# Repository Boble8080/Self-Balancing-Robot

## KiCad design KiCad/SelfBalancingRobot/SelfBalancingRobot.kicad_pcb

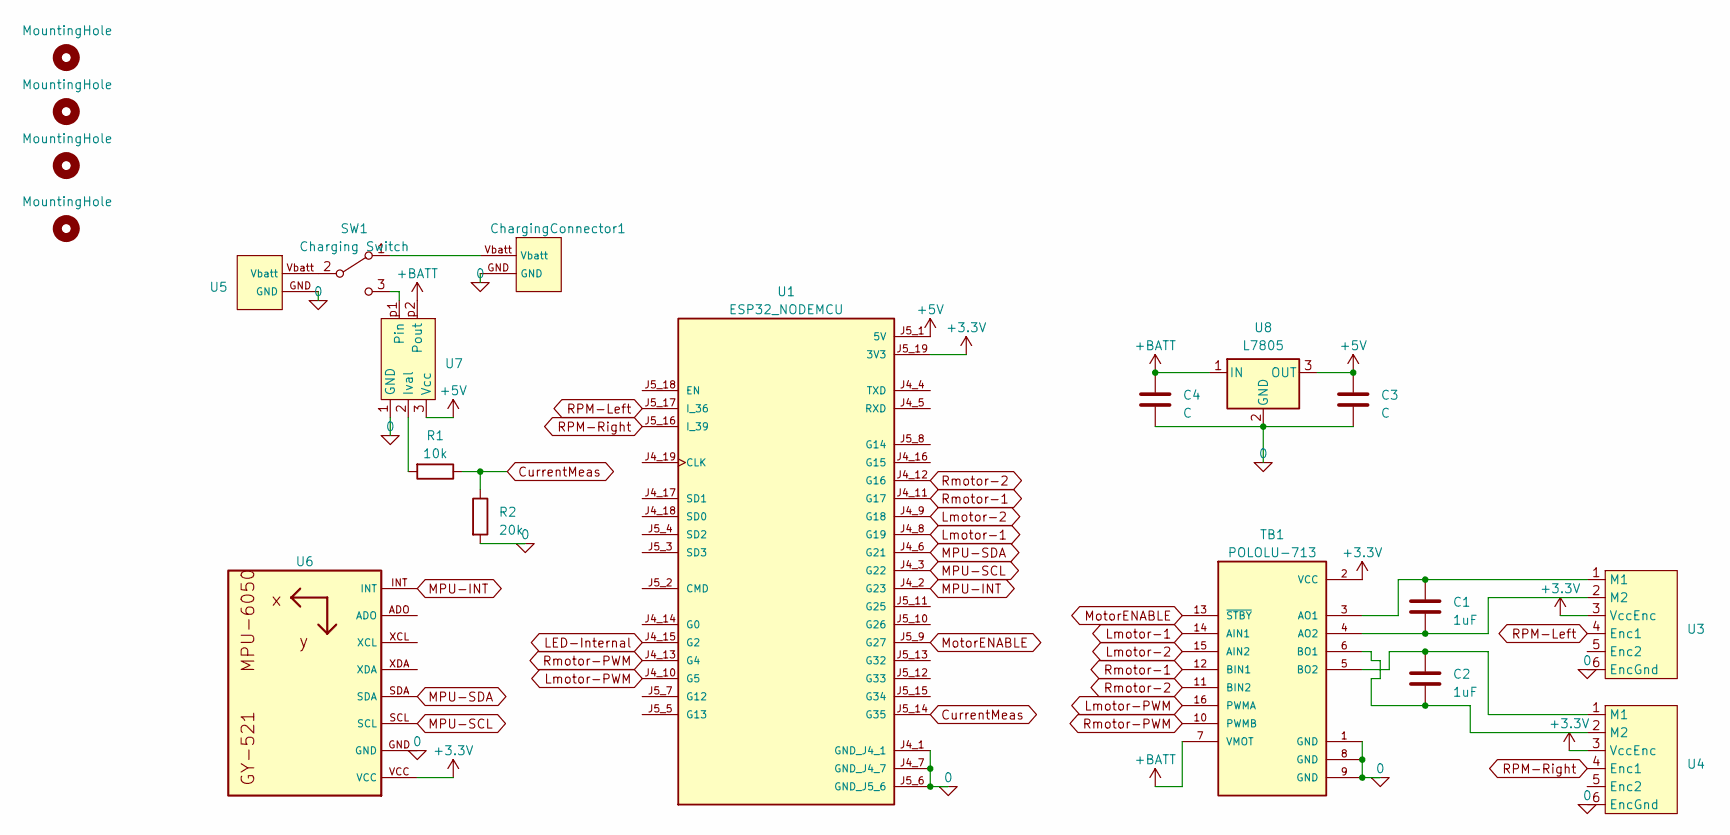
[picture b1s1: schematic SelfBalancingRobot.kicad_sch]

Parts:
C1, C2: 1uF; C_Disc_D6.0mm_W4.4mm_P5.00mm
C3, C4: C; CP_Radial_D6.3mm_P2.50mm
ChargingConnector1: ChargingConnector
H1, H2, H3, H4: MountingHole; MountingHole_3.2mm_M3_DIN965_Pad_TopBottom
R1: 10k; R_Axial_DIN0207_L6.3mm_D2.5mm_P7.62mm_Horizontal
R2: 20k; R_Axial_DIN0207_L6.3mm_D2.5mm_P7.62mm_Horizontal
SW1: Charging Switch; PhoenixContact_MSTBA_2,5_3-G-5,08_1x03_P5.08mm_Horizontal
TB1: POLOLU-713; SHIELD_POLOLU-713
U1: ESP32_NODEMCU; MODULE_ESP32_NODEMCU
U3, U4: V-TecMotorHeader
U5: BatteryConnector
U6: MPU-6050-External
U7: CurrentMeter
U8: L7805; TO-220-3_Horizontal_TabDown

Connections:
0: C3.2, C4.2, ChargingConnector1.GND, R2.2, TB1.1 (GND), TB1.8 (GND), TB1.9 (GND), U1.J4_1 (GND_J4_1), U1.J4_7 (GND_J4_7), U1.J5_6 (GND_J5_6), U3.6 (EncGnd), U4.6 (EncGnd), U5.GND, U6.GND, U7.1 (GND), U8.2 (GND)
+3.3V: TB1.2 (VCC), U1.J5_19 (3V3), U3.3 (VccEnc), U4.3 (VccEnc), U6.VCC
+5V: C3.1, U1.J5_1 (5V), U7.3 (Vcc), U8.3 (OUT)
+BATT: C4.1, TB1.7 (VMOT), U7.p2 (Pout), U8.1 (IN)
CurrentMeas: R1.1, R2.1, U1.J5_14 (G35)
LED-Internal: U1.J4_15 (G2)
Lmotor-1: TB1.14 (AIN1), U1.J4_8 (G19)
Lmotor-2: TB1.15 (AIN2), U1.J4_9 (G18)
Lmotor-PWM: TB1.16 (PWMA), U1.J4_10 (G5)
MPU-INT: U1.J4_2 (G23), U6.INT
MPU-SCL: U1.J4_3 (G22), U6.SCL
MPU-SDA: U1.J4_6 (G21), U6.SDA
MotorENABLE: TB1.13 (~STBY), U1.J5_9 (G27)
unnamed: ChargingConnector1.Vbatt, SW1.1 (A)
unnamed: SW1.2 (B), U5.Vbatt
unnamed: SW1.3 (C), U7.p1
unnamed: C1.1, TB1.3 (AO1), U3.1 (M1)
unnamed: C1.2, TB1.4 (AO2), U3.2 (M2)
unnamed: C2.2, TB1.6 (BO1), U4.2 (M2)
unnamed: C2.1, TB1.5 (BO2), U4.1 (M1)
unnamed: R1.2, U7.2 (Ival)
RPM-Left: U1.J5_17 (I_36), U3.4 (Enc1)
RPM-Right: U1.J5_16 (I_39), U4.4 (Enc1)
Rmotor-1: TB1.12 (BIN1), U1.J4_11 (G17)
Rmotor-2: TB1.11 (BIN2), U1.J4_12 (G16)
Rmotor-PWM: TB1.10 (PWMB), U1.J4_13 (G4)

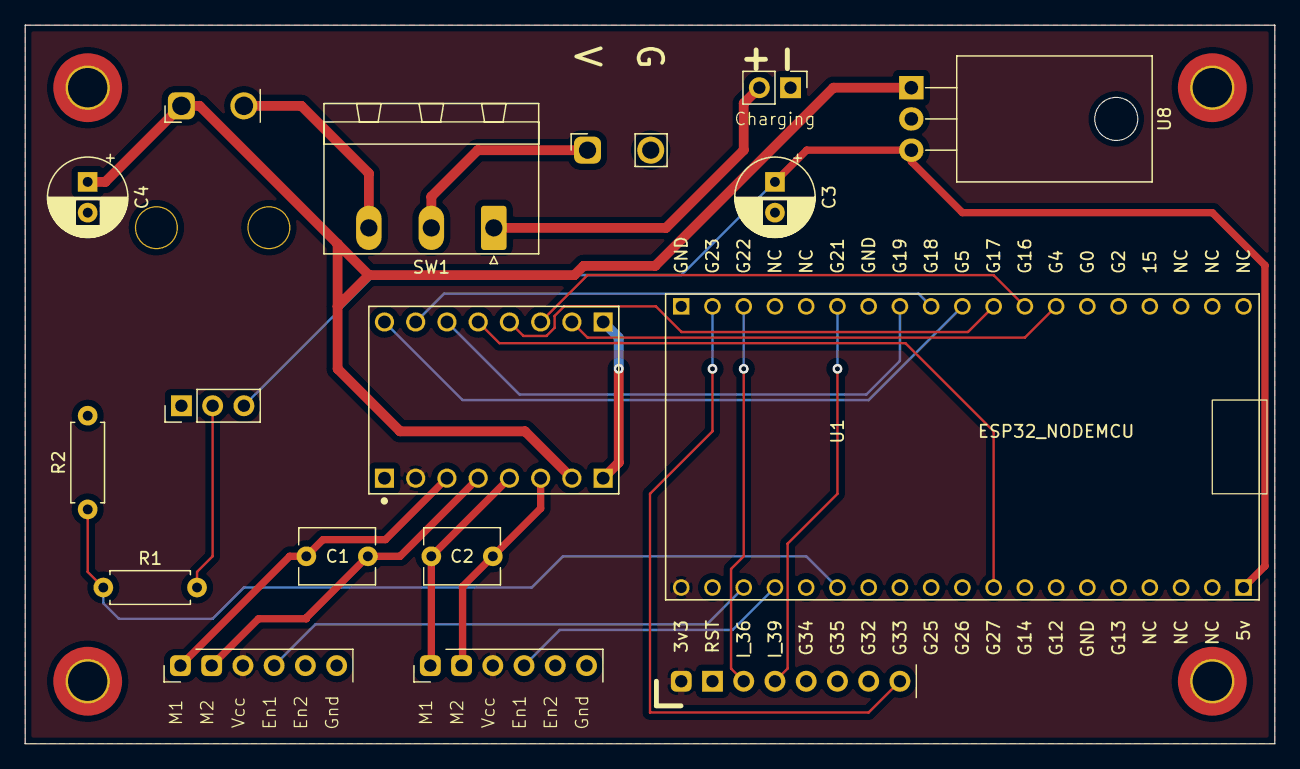
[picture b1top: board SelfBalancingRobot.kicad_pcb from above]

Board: 2 copper layers, 101.6 x 58.4 mm, 20 parts (0 on the bottom side), 25 nets.

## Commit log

2023-03-20 added stationary test
2023-03-26 added debug
2023-03-27 motor test and step
2023-03-28 ltspice battery test
2023-04-04 apptest
2023-04-04 newMPU and 2 motors
2023-04-06 rmpmeter1
2023-04-06 motorOOP
2023-04-06 comment
2023-04-08 OOP fix
2023-04-08 oopwah
2023-04-11 encoder double code
2023-04-11 stationarywithmotors
2023-04-13 kicad
2023-04-17 kicad parts
2023-04-18 kicad layout finished1
2023-04-20 kicad done and pid integrated
2023-04-20 Working PID
2023-04-21 pidFix
2023-04-21 bluetooth
2023-04-21 linearCal
2023-04-21 gitMess
2023-04-24 stationaryFixAndBluetooth
2023-04-27 pwmTest
2023-04-27 PIDtuning
2023-05-01 int16 fix
2023-05-03 moved serial and falltest to functions
2023-05-03 bluetoothFormating
2023-05-05 bluetooth refactor
2023-05-05 kicad zip
2023-05-05 pid2
2023-05-09 visual
2023-05-16 cascade
2023-05-16 final
2023-05-16 finalGitMerge
2023-05-16 casc
2023-05-17 pre-presentation
